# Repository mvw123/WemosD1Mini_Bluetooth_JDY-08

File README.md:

Wemos D1 Mini JDY-08 Bluetooth BTLE shield
==========================================

WORK IN PROGRESS - Not tested or verified in any way shape or form.

CAD B

Not released yet

Updated JDY-08 from library

CAD A

Released for manufacture at OSH park 6 Nov 2017

To be used for BLE sensor hub project in combination with sensor nodes.

Software needs writing/ modifying from existing software.

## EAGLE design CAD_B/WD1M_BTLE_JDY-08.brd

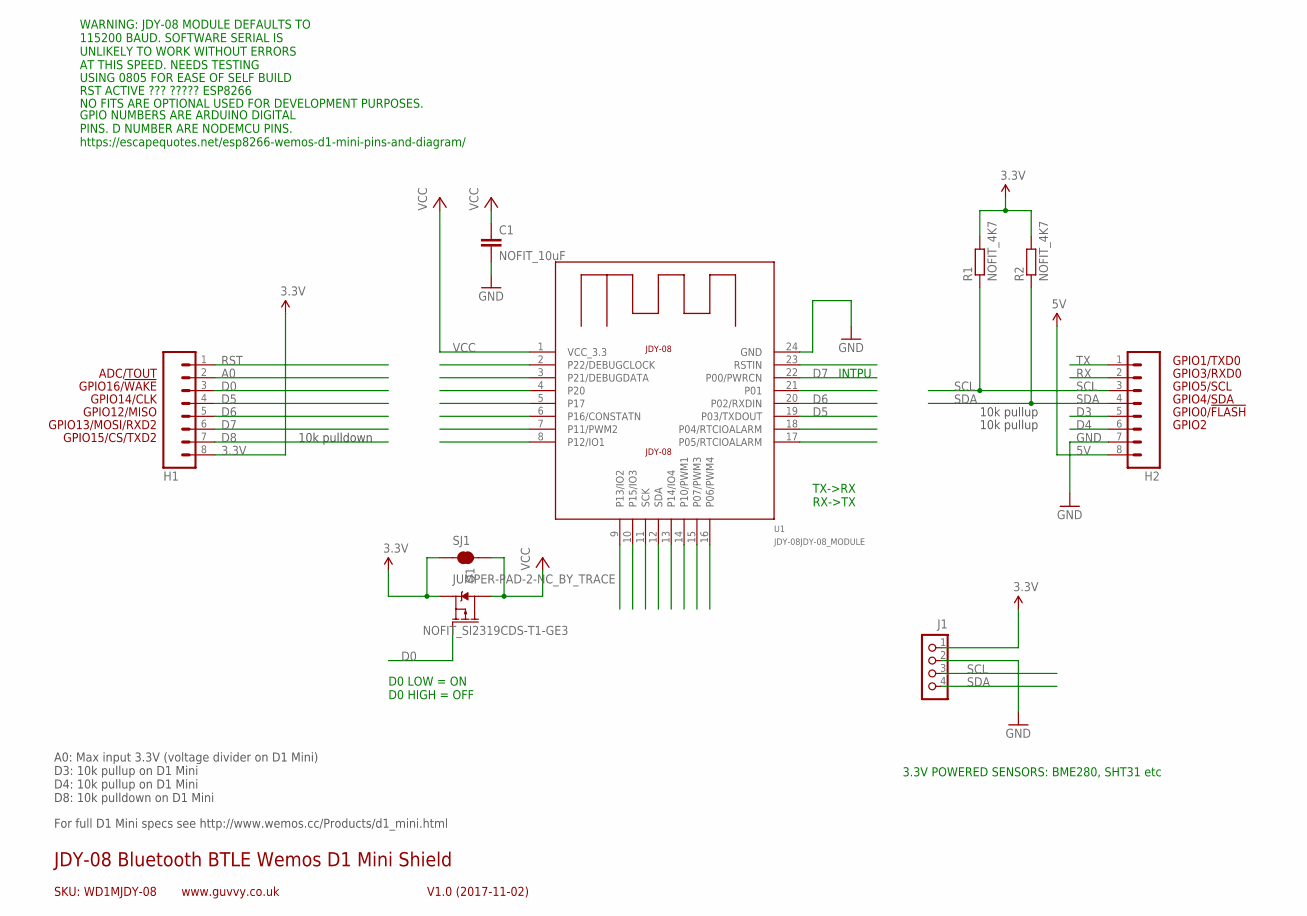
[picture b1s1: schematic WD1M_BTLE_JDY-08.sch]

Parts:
C1: NOFIT_10uF; C0805K
H1, H2: M08; 1X08
J1: CON_HEADER_1X04; M1X4
Q1: NOFIT_SI2319CDS-T1-GE3; SOT23-3
R1, R2: NOFIT_4K7; R0805
SJ1: JUMPER-PAD-2-NC_BY_TRACE; PAD-JUMPER-2-NC_BY_TRACE_YES_SILK
U1: JDY-08JDY-08_MODULE; JDY-08

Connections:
3.3V: H1.8, J1.1, Q1.2 (S), R1.2, R2.2, SJ1.1
5V: H2.8
A0: H1.2
D0: H1.3, Q1.1 (G)
D3: H2.5
D4: H2.6
D5: H1.4, U1.19 (P03/TXDOUT)
D6: H1.5, U1.20 (P02/RXDIN)
D7: H1.6, U1.22 (P00/PWRCN)
D8: H1.7
GND: C1.2, H2.7, J1.2, U1.24 (GND)
RST: H1.1
RX: H2.2
SCL: H2.3, J1.3, R1.1
SDA: H2.4, J1.4, R2.1
TX: H2.1
VCC: C1.1, Q1.3 (D), SJ1.2, U1.1 (VCC_3.3)

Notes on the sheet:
GPIO2
GPIO0/!FLASH
GPIO12/MISO
GPIO4/SDA
GPIO5/SCL
GPIO3/RXD0
GPIO1/TXD0
GPIO13/MOSI/RXD2
GPIO14/CLK
GPIO15/CS/TXD2
GPIO16/!WAKE
SKU: WD1MJDY-08
JDY-08 Bluetooth BTLE Wemos D1 Mini Shield
V1.0 (2017-11-02)
www.guvvy.co.uk
ADC/TOUT
A0: Max input 3.3V (voltage divider on D1 Mini) D3: 10k pullup on D1 Mini D4: 10k pullup on D1 Mini D8: 10k pulldown on D1 Mini
10k pulldown
10k pullup
For full D1 Mini specs see http://www.wemos.cc/Products/d1_mini.html
RST ACTIVE ??? ????? ESP8266
USING 0805 FOR EASE OF SELF BUILD
TX->RX RX->TX
INTPU
D0 LOW = ON D0 HIGH = OFF
3.3V POWERED SENSORS: BME280, SHT31 etc
WARNING: JDY-08 MODULE DEFAULTS TO 115200 BAUD. SOFTWARE SERIAL IS UNLIKELY TO WORK WITHOUT ERRORS AT THIS SPEED. NEEDS TESTING
NO FITS ARE OPTIONAL USED FOR DEVELOPMENT PURPOSES.
GPIO NUMBERS ARE ARDUINO DIGITAL PINS. D NUMBER ARE NODEMCU PINS. https://escapequotes.net/esp8266-wemos-d1-mini-pins-and-diagram/

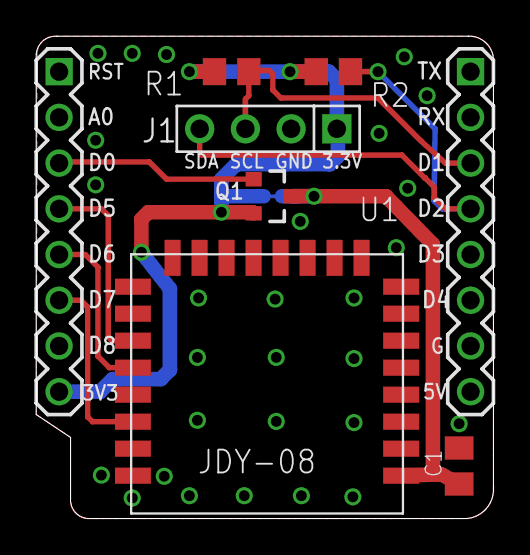
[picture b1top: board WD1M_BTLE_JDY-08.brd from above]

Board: 2 copper layers, 25.4 x 26.8 mm, 9 parts (1 on the bottom side), 9 nets.

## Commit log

2017-11-08 First commit for CAD A
    CAD A board sent for manufacture.
2017-11-16 Resistor value update
2018-01-19 changed directory structure and added new CAD B
2019-02-10 adding latest unknown changes

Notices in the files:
parts and their libraries:
freetronics-original: Licensing: CC v3.0 Share-Alike You are welcome to use this library for commercial purposes.
SparkFun-DiscreteSemi: Licensing: Creative Commons ShareAlike 4.0 International - https://creativecommons.org/licenses/by-sa/4.0
